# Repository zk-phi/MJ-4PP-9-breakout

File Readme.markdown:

# MJ-4PP-9 Breakout Board

ブレッドボード・自作キーボード開発に特化した MJ-4PP-9 のブレイクアウトボードです。

MJ-4PP-9 をブレッドボードに刺せます。

電源ライン用の２ピンヘッダを実装すると、自作キーボードで電源ラインとして使用されることの多い `T`, `S` をブレッドボードの電源ラインに直接供給することができます。

普通に音声用として使用する場合は２ピンヘッダは実装しなくても使えます。

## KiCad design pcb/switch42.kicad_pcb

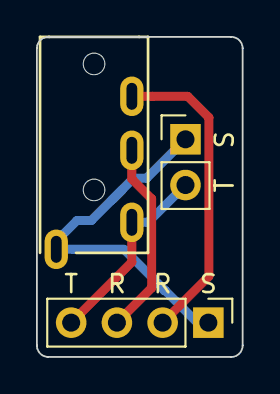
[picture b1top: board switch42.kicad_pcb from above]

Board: 2 copper layers, 11.4 x 17.8 mm, 3 parts (0 on the bottom side), 4 nets.

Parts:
J1: MJ-4PP-9; MJ-4PP-9-irreversible
J2: Conn_01x02; PinHeader_1x02_P2.54mm_Vertical
J3: Conn_01x04; PinHeader_1x04_P2.54mm_Vertical

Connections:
unnamed: J1.A, J2.1, J3.1
unnamed: J1.B, J3.2
unnamed: J1.C, J3.3
unnamed: J1.D, J2.2, J3.4

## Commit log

2020-06-01 Add pcb
2020-06-01 Add readme
2020-06-01 add dimensions
